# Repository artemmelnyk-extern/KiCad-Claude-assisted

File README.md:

# Safety inputs for Arduino UNO: 2 e-stops + 2 lidars through PC817

An Arduino UNO shield with **four isolated 24 V inputs**: two emergency-stop buttons (one
normally-closed contact each) and two safety-lidar outputs. Each input goes through a PC817
optocoupler, so the 24 V side is electrically isolated from the microcontroller. It works unchanged on
the **UNO R4 WiFi** (5 V logic) and the **UNO Q** (3.3 V logic).

The KiCad schematic and board in this repository are **generated by Python scripts**. The scripts are
the source; the KiCad files are their output.

## The circuit

All four channels are the same; only the terminal wiring and the resistor value differ.

```
 e-stop:  24V ─[F1 T2A]─► ESn+ ──(button, NC)── ESn ─┐
 lidar:   lidar output (24 V when the zone is clear) ─ Ln ─┤
                                                      │
        ───[R]───┬─[LED]─► PC817 pin 1      pin 4 ─┬──────┬─ D2..D5
                 │                                  │      │
             [1N4148]                            [10k]   [C 100n, optional]
                 │                                  │      │
 0V ─────────────┴───────── PC817 pin 2           IOREF    │
                                             pin 3 ────────┴─ GND
```

| Pin | Input | Terminals | Series resistor (½ W) | Current |
|---|---|---|---|---|
| D2 | e-stop 1 | `ES1+`, `ES1` | R1 = 3.3 kΩ | 6.3 mA |
| D3 | e-stop 2 | `ES2+`, `ES2` | R2 = 3.3 kΩ | 6.3 mA |
| D4 | lidar 1 | `L1`, `0V` | R3 = 4.7 kΩ | 4.4 mA |
| D5 | lidar 2 | `L2`, `0V` | R4 = 4.7 kΩ | 4.4 mA |

| State | LED | Pin |
|---|---|---|
| Current flows: button released, or lidar zone clear | lit | **LOW = OK** |
| No current: button pressed, zone occupied, wire cut, connector unplugged, 24 V lost, fuse blown | off | **HIGH = stop** |

Every wiring failure reads as "stop".

- **The 24 V comes from an external source.** The board has none of its own: connect the source's
  plus to the `24V` screw and its minus to a `0V` screw. The board draws about 13 mA from it (the two
  e-stop loops). The lidars must share this same 0 V. The schematic draws the source in the
  "EXTERNAL" box.
- **The e-stop buttons are external.** The schematic draws them left of the terminal block, in a
  dashed box marked "EXTERNAL - not on the board": S1 between `ES1+` and `ES1`, S2 between `ES2+` and
  `ES2`, each with one normally-closed contact (two terminals). They are drawings only, so they
  appear in neither the netlist nor the board. Which button is front and which is rear is a choice
  made at installation; the sheet labels S1 front and S2 rear.
- **Terminal block J1**, top to bottom: `24V`, `0V`, `L1`, `ES2+`, `ES2`, `ES1+`, `ES1`, `L2`, `0V`.
  The order follows the channels on the board.
- **F1 (T2A)** protects the 24 V wires that leave the board for the buttons.
- **E-stop loops carry 6.3 mA** because switch contacts need a minimum current to stay reliable (often
  about 5 mA at 24 V; check the button's data sheet). A lidar output is electronic and needs none.
- **R1–R4 must be real ½ W parts** (body about 9 × 3.2 mm). At 28.8 V a 3.3 kΩ dissipates 0.20 W
  (40 % of ½ W) and a 4.7 kΩ 0.14 W (28 %). A ¼ W-size resistor (6 × 2.3 mm) sold as ½ W would run
  at 80 % of its real rating: measure the body before fitting. The 10 kΩ pull-ups R5–R8 dissipate
  2.5 mW; any rating will do.
- **C1–C4 (100 nF) are optional.** With the 10 kΩ pull-up they form a 1 ms filter on the rising
  (stop) edge: an opening shorter than about 1.5 ms never reaches the Arduino's HIGH threshold, and
  every real stop is seen about 1.6 ms later. Fitted, they remove contact bounce and a lidar's
  output test pulses in hardware; they also hide those short openings from the firmware, which can
  then no longer count them. Leave them out to observe the raw signal. The timing figures are
  calculated, not measured.
- The 1N4148 protects the LEDs against a reversed connection (the PC817 LED tolerates only 6 V).
- `0V` (24 V side) and `GND` (Arduino) are separate nets. Do not join them: that is the isolation.
  The lidars' 0 V must be connected to this board's `0V`.
- Each input is **single-channel**. A short across a button's two wires, or a shorted optocoupler
  output, reads as "OK" and is not detected. This is not a certified safety function.

## One board, two Arduinos

The pull-ups are tied to the header's **IOREF** pin, not to 5V. IOREF carries the logic voltage of
whichever board is plugged in, so the outputs swing to 5 V on a UNO R4 WiFi and to 3.3 V on a UNO Q,
with no jumper and no part change. The 24 V side is identical for both.

| | UNO R4 WiFi | UNO Q |
|---|---|---|
| Logic voltage (IOREF) | 5 V | 3.3 V |
| Pull-up current through 10 kΩ | 0.5 mA | 0.33 mA |
| Output LOW (PC817 saturated) | ≤ 0.2 V | ≤ 0.2 V |

Only pins that exist on every UNO-format board are used. The UNO Q figures come from its published
specification and have not been tried on hardware here: check the IOREF voltage with a multimeter
before plugging the bench onto a UNO Q.

## Repository layout

| Path | Content |
|---|---|
| `generate.py` | writes the schematic, project and symbol library in `kicad/`. Standard-library Python 3 |
| `generate_pcb.py` | writes the board `kicad/pc817_bench.kicad_pcb`: placement and routing. Needs KiCad's Python (`pcbnew`) |
| `kicad/` | generated KiCad project: open `pc817_bench.kicad_pro` |
| `docs/` | schematic (PDF, SVG), board layers (SVG), 3D view (PNG) |
| `firmware/pc817_two_inputs/` | Arduino sketch that prints every edge with its timing |
| `generate_protoboard.py` | writes `protoboard/`: the same circuit as a hole-by-hole build plan for a proto shield with isolated pads, checked against the schematic's netlist. Needs matplotlib |
| `protoboard/` | [BUILD.md](protoboard/BUILD.md) (parts, bridges, wires), `layout.png`, `layout.pdf` (1:1) |
| `check.sh` | regenerate everything, run KiCad's schematic and board rule checks, export `docs/` |

## Use

```bash
./check.sh     # needs kicad-cli and KiCad's Python, KiCad 9 or later
```

With the Flatpak build of KiCad:

```bash
KICAD_CLI="flatpak run --command=kicad-cli --filesystem=$PWD org.kicad.KiCad" \
KICAD_PYTHON="flatpak run --command=python3 --filesystem=$PWD org.kicad.KiCad" ./check.sh
```

To change the circuit or the layout, edit the scripts and run `check.sh` again. Edits made in the
KiCad editors are overwritten by the next run.

## The board

A two-layer, through-hole Arduino UNO shield, 66 × 53 mm, four channels at a 10 mm pitch.

- 24 V parts on the left, logic on the right. The gap under the optocouplers is the isolation
  barrier. One logic track (D5) runs in that gap on the solder side, 4.3 mm from the 24 V pins.
- Rows, top to bottom: lidar 1, e-stop 2, e-stop 1, lidar 2. This order lets each output reach its
  header pin without crossing another.
- The 9-way screw terminal (3.5 mm pitch) runs down the left edge with the fuse above it. On a
  UNO R4 WiFi this is above the USB-C connector, and the lowest terminals reach the power jack.
- Signal tracks are 0.5 mm, the fused 24 V tracks 1 mm. The 24 V return runs on the solder side.
- Part references of the resistors, diodes and optocouplers are printed under the parts.
- The optional capacitors stand right of the optocouplers, across pins 4 and 3.
- The library footprint `Module:Arduino_UNO_R3` is placed **flipped to the back side**, because a
  shield sits above the Arduino. Unflipped, the shield comes out mirrored. Its courtyard is removed,
  since the shield's parts are meant to be inside the Arduino's outline.
- Of the three GND header pins, the two on the power header are used.

## How the generators work

`generate_pcb.py` uses KiCad's `pcbnew` Python module: it loads the library footprints named in the
schematic, assigns nets from the exported netlist, places each part at fixed coordinates and adds
the tracks segment by segment. There is no autorouter.

`generate.py` uses no KiCad API. It writes KiCad's text file format (S-expressions) directly:

- the symbols (resistor, LED, diode, fuse, PC817, terminal block, Arduino UNO header) are defined in the script and embedded in the
  schematic, and also written to `kicad/bench.kicad_sym`;
- `place()`, `wire()`, `label()` and `junction()` append one schematic item each;
- `channel(k, y)` draws one complete input channel, and is called twice.

## Limits

- The board passes KiCad's design-rule check with default rules (one expected warning: the Arduino
  footprint differs from its library copy). **It has not been manufactured or assembled.** Before
  ordering, check the header orientation against a real Arduino using a 1:1 print, and the height of
  the terminal block's solder pins above the Arduino's connectors.
- No mounting holes, no test points, no copper zones.
- The files are written in the KiCad 7 format. KiCad 8 and later open them and show a notice that the
  file will be converted when saved. Checked with KiCad 10.0.6: loads, 0 rule-check violations.
- The Arduino is drawn as one symbol with the standard UNO shield header. Only IOREF, GND, D2 and D3
  are used; the other pins carry no-connect marks. Its pin numbers are the pad numbers of the library footprint.
- A shorted optocoupler output transistor also reads as "released", undetected.

## Datasheet

PC817: 4-pin DIP, pin 1 anode, 2 cathode, 3 emitter, 4 collector; current transfer ratio 50–600 % at
5 mA; isolation 5000 Vrms. Datasheets are available from Sharp and from second-source manufacturers.

## This branch: the proto-shield build

**On this branch the KiCad files describe a hand-built board, not a board to manufacture.** The circuit
is the one on `main`; three things differ so that it fits a proto shield with isolated pads on a
2.54 mm grid:

- resistors and the 1N4148 are mounted upright (2.54 mm footprints);
- the terminals are three 3-way screw blocks at 2.54 mm, as soldered on the built board: `24V`, `0V`,
  `0V` (supply), `ES+`, `ES1`, `ES2` (e-stops, sharing the `ES+` screw), `0V`, `L1`, `L2` (lidars);
- `kicad/pc817_bench.kicad_pcb` is a **model of the build**: parts on the grid, solder bridges and
  bare-wire runs as tracks on the solder side, insulated wires as lines on the `Cmts.User` layer.

| File | Content |
|---|---|
| [protoboard/BUILD.md](protoboard/BUILD.md) | parts with their holes, bridges, bare-wire runs, wires |
| `protoboard/layout.png`, `layout.pdf` | the plan as a drawing; the PDF prints at 1:1 |
| `generate_protoboard.py` | the plan itself; checks that the joined holes form the schematic's nets |
| `generate_pcb.py` | builds the KiCad model from the plan |

In KiCad's board editor the insulated wires appear as ratsnest lines, and the design-rule check
reports one "unconnected" item per wire plus one for the two GND header pins. That is expected;
`check.sh` verifies the count and that the model matches the schematic.

The plan is laid out for the **green ElectroCookie "Uno ProtoShield Universal"** and names every hole
by the column numbers printed on that board (1-20) and a row count from the printed edge. The hole
map was read from a photo and then confirmed on the real board (pad count, header pads, jack
clearance).

## Licence

MIT, see [LICENSE](LICENSE). It covers the script, the sketch and the generated KiCad files.

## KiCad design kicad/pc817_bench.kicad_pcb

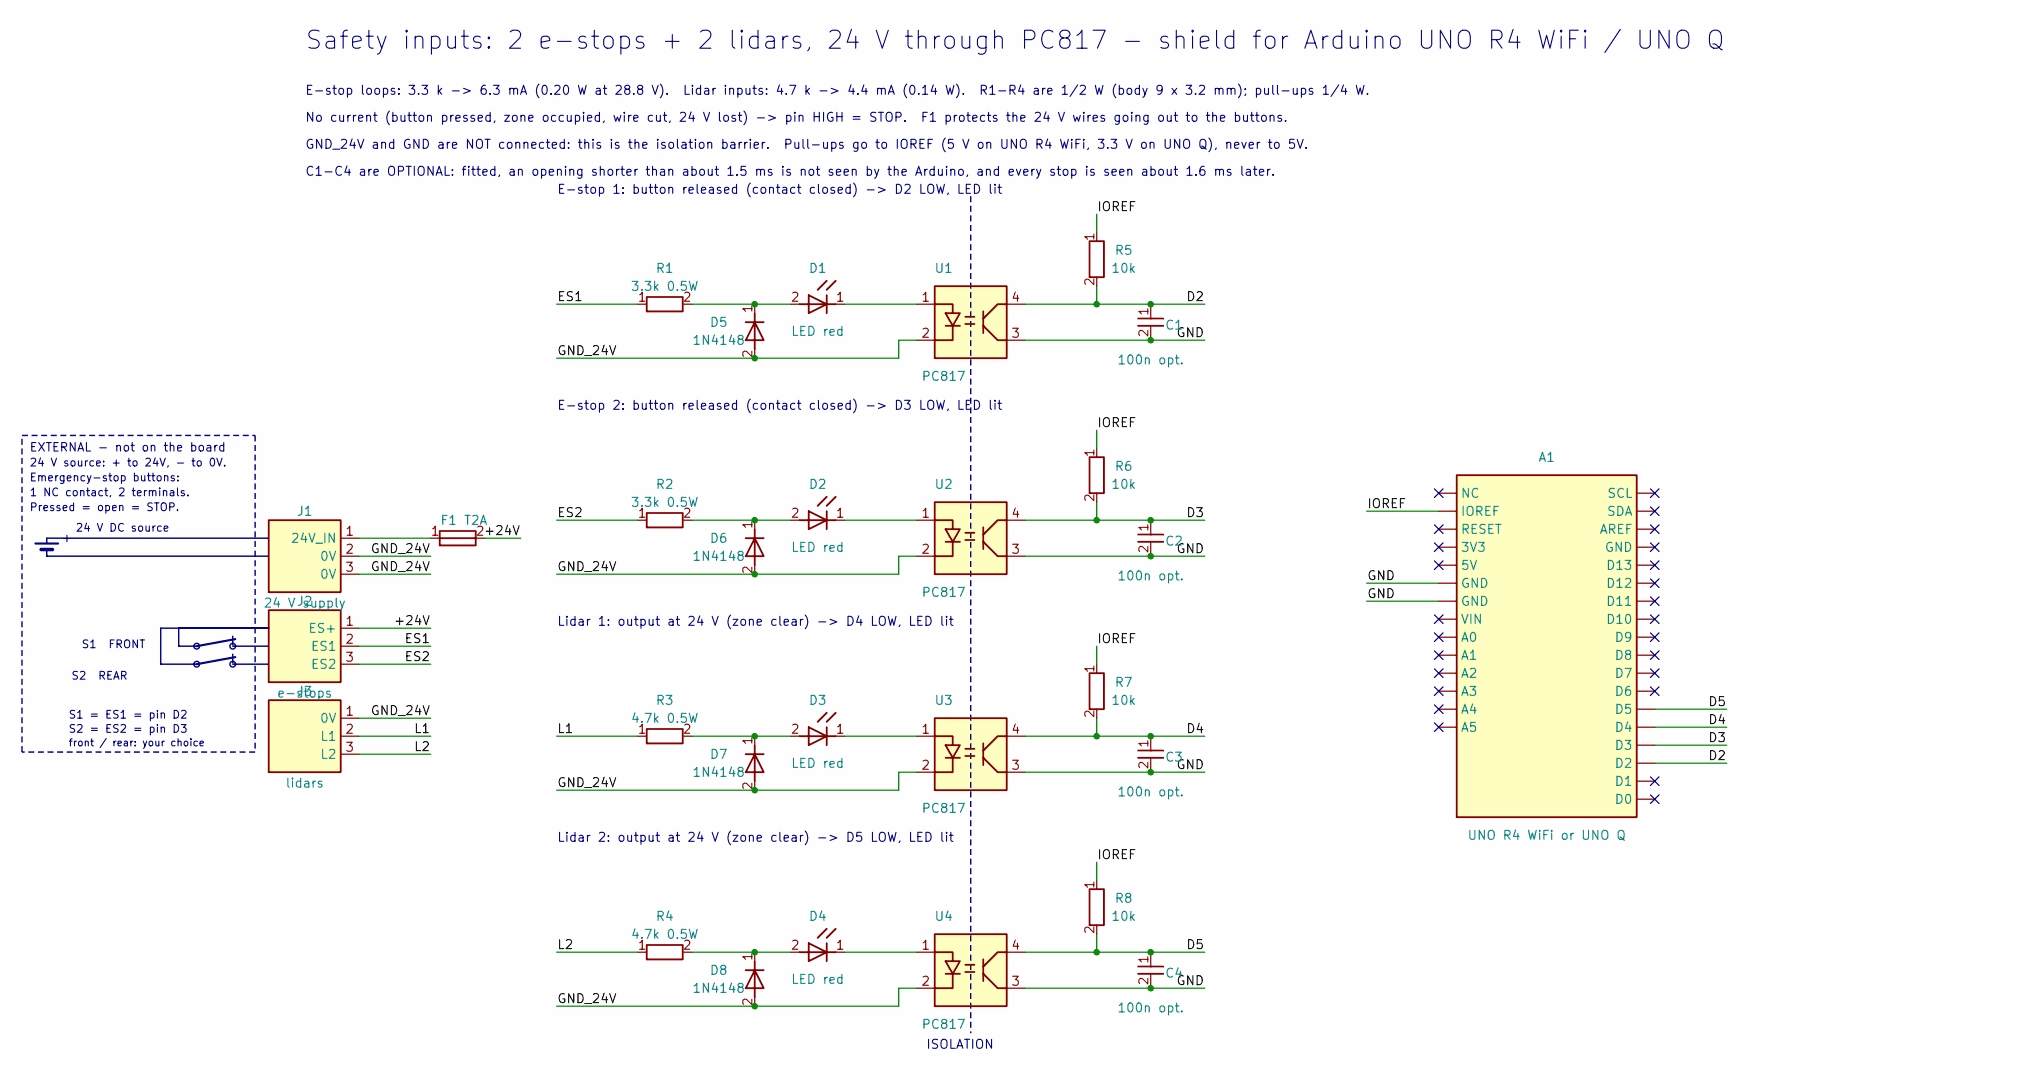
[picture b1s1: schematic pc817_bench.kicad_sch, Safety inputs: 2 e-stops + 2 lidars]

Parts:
A1: UNO R4 WiFi or UNO Q; Arduino_UNO_R3
C1, C2, C3, C4: 100n opt.; C_Disc_D3.0mm_W1.6mm_P2.50mm
D1, D2, D3, D4: LED red; LED_D3.0mm
D5, D6, D7, D8: 1N4148; D_DO-35_SOD27_P2.54mm_Vertical_CathodeUp
F1: T2A; R_Axial_DIN0309_L9.0mm_D3.2mm_P12.70mm_Horizontal
J1: 24 V supply; TerminalBlock_Xinya_XY308-2.54-3P_1x03_P2.54mm_Horizontal
J2: e-stops; TerminalBlock_Xinya_XY308-2.54-3P_1x03_P2.54mm_Horizontal
J3: lidars; TerminalBlock_Xinya_XY308-2.54-3P_1x03_P2.54mm_Horizontal
R1, R2: 3.3k 0.5W; R_Axial_DIN0309_L9.0mm_D3.2mm_P2.54mm_Vertical
R3, R4: 4.7k 0.5W; R_Axial_DIN0309_L9.0mm_D3.2mm_P2.54mm_Vertical
R5, R6, R7, R8: 10k; R_Axial_DIN0207_L6.3mm_D2.5mm_P2.54mm_Vertical
U1, U2, U3, U4: PC817; DIP-4_W7.62mm

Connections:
/+24V: F1.2, J2.1 (ES+)
/D2: A1.17 (D2), C1.1, R5.2, U1.4 (C)
/D3: A1.18 (D3), C2.1, R6.2, U2.4 (C)
/D4: A1.19 (D4), C3.1, R7.2, U3.4 (C)
/D5: A1.20 (D5), C4.1, R8.2, U4.4 (C)
/ES1: J2.2 (ES1), R1.1
/ES2: J2.3 (ES2), R2.1
/GND: A1.6 (GND), A1.7 (GND), C1.2, C2.2, C3.2, C4.2, U1.3 (E), U2.3 (E), U3.3 (E), U4.3 (E)
/GND_24V: D5.2 (A), D6.2 (A), D7.2 (A), D8.2 (A), J1.2 (0V), J1.3 (0V), J3.1 (0V), U1.2 (K), U2.2 (K), U3.2 (K), U4.2 (K)
/IOREF: A1.2 (IOREF), R5.1, R6.1, R7.1, R8.1
/L1: J3.2 (L1), R3.1
/L2: J3.3 (L2), R4.1
unnamed: D1.2 (A), D5.1 (K), R1.2
unnamed: D1.1 (K), U1.1 (A)
unnamed: D2.2 (A), D6.1 (K), R2.2
unnamed: D2.1 (K), U2.1 (A)
unnamed: D3.2 (A), D7.1 (K), R3.2
unnamed: D3.1 (K), U3.1 (A)
unnamed: D4.2 (A), D8.1 (K), R4.2
unnamed: D4.1 (K), U4.1 (A)
unnamed: F1.1, J1.1 (24V_IN)

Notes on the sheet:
E-stop 1: button released (contact closed) -> D2 LOW, LED lit
E-stop 2: button released (contact closed) -> D3 LOW, LED lit
Lidar 1: output at 24 V (zone clear) -> D4 LOW, LED lit
Lidar 2: output at 24 V (zone clear) -> D5 LOW, LED lit
24 V DC source
S1 FRONT
S2 REAR
EXTERNAL - not on the board
24 V source: + to 24V, - to 0V.
Emergency-stop buttons:
1 NC contact, 2 terminals.
Pressed = open = STOP.
S1 = ES1 = pin D2
S2 = ES2 = pin D3
front / rear: your choice
Safety inputs: 2 e-stops + 2 lidars, 24 V through PC817 - shield for Arduino UNO R4 WiFi / UNO Q
E-stop loops: 3.3 k -> 6.3 mA (0.20 W at 28.8 V). Lidar inputs: 4.7 k -> 4.4 mA (0.14 W). R1-R4 are 1/2 W (body 9 x 3.2 mm); pull-ups 1/4 W.
C1-C4 are OPTIONAL: fitted, an opening shorter than about 1.5 ms is not seen by the Arduino, and every stop is seen about 1.6 ms later.
No current (button pressed, zone occupied, wire cut, 24 V lost) -> pin HIGH = STOP. F1 protects the 24 V wires going out to the buttons.
GND_24V and GND are NOT connected: this is the isolation barrier. Pull-ups go to IOREF (5 V on UNO R4 WiFi, 3.3 V on UNO Q), never to 5V.
ISOLATION

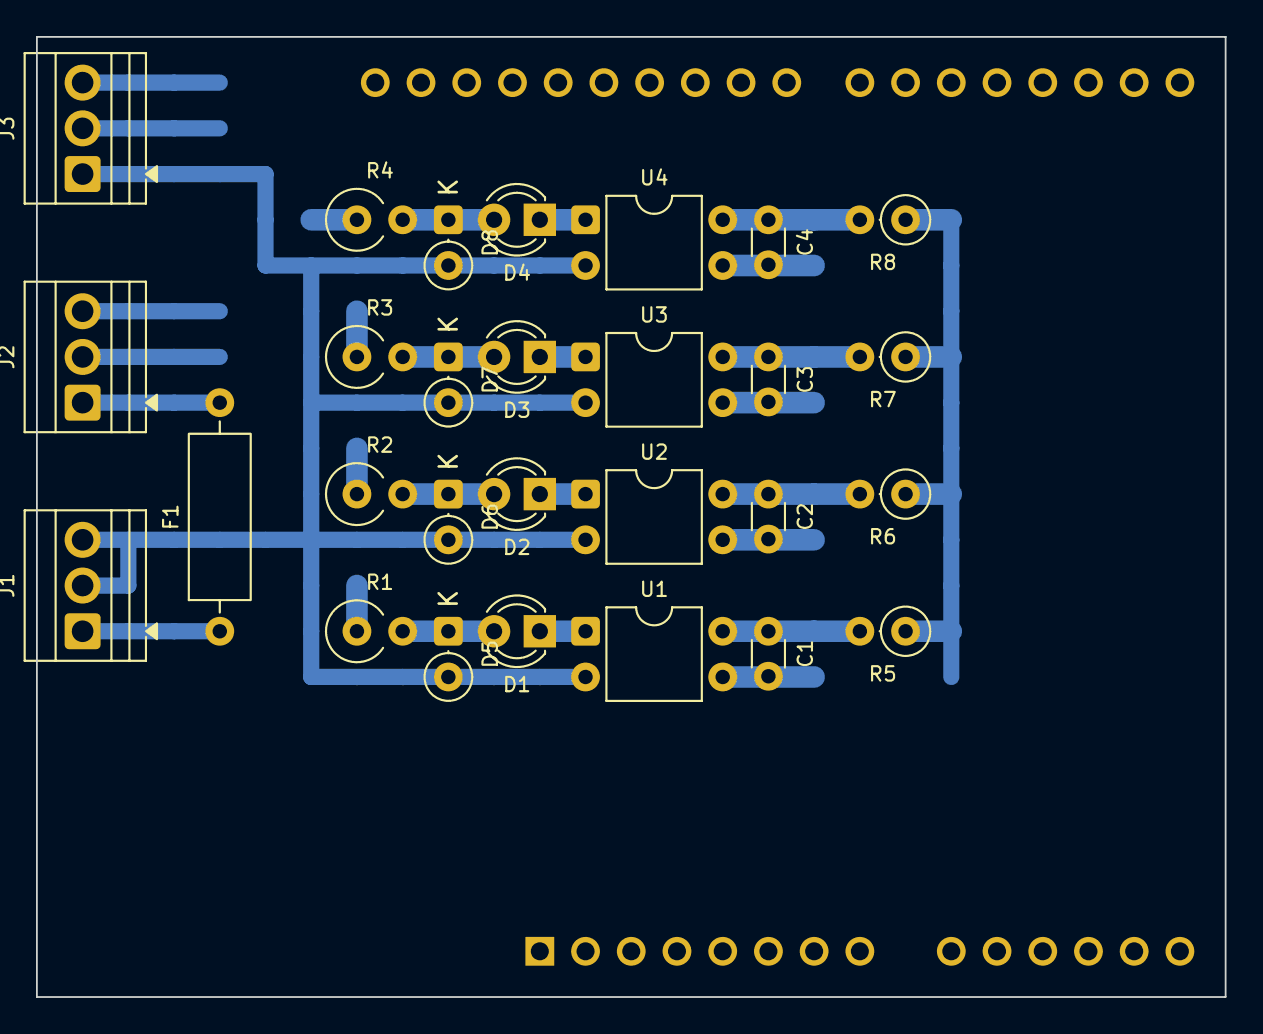
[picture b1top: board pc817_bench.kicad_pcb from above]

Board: 2 copper layers, 66.0 x 53.3 mm, 29 parts (1 on the bottom side), 21 nets.
